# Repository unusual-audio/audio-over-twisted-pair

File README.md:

# Simple audio over twisted pair adapter

A basic adapter box that can route 4 differential audio signals on TRS connectors over twisted pair cable (ideally S/FTP).

## Bill of materials (per unit)

- 1× Main PCB ([gerber files](https://github.com/unusual-audio/audio-over-twisted-pair/releases/download/revision1/PCB.zip))
- 1× Front panel PCB ([gerber files](https://github.com/unusual-audio/audio-over-twisted-pair/releases/download/revision1/Front.Panel.zip))
- 1× Rear panel PCB ([gerber files](https://github.com/unusual-audio/audio-over-twisted-pair/releases/download/revision1/Back.Panel.zip))
- 1× [Adafruit 2230](https://www.mouser.de/ProductDetail/485-2230) enclosure
- 1× [Amphenol RJHSE-5380](https://www.mouser.de/ProductDetail/523-RJHSE-5380) RJ45 connector
- 4× [Neutrik NRJ6HF](https://www.mouser.de/ProductDetail/550-20311) TRS connector
- 4× [Neutrik NRJ-NUT-B](https://www.mouser.de/ProductDetail/550-1005) nut for TRS connector
- 8× M2.5x7 machine screw (Adafruit supplies counterunk screws, unsuitable for PCB panels)
- 4× Self-adhesive rubber feet (e.g. 3M Bumpons SJ 5076)

## Caveats

- This is a hobby project. Recreate at your own risk. (but if you do, send pictures to <unusualaudio@protonmail.com>)
- These are not necessarily compatible with similar commercial products as the wiring is not standardised.

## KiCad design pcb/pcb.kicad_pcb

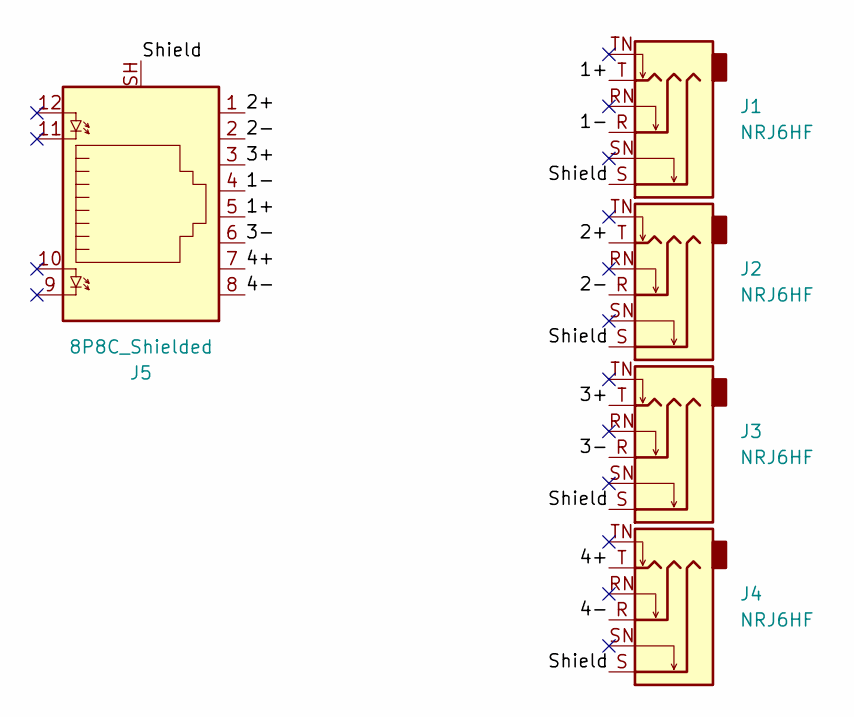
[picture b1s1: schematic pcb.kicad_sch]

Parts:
J1, J2, J3, J4: NRJ6HF; Jack_6.35mm_Neutrik_NRJ6HF_Horizontal_No_Outline
J5: 8P8C_Shielded; RJ45_Amphenol_RJHSE538X

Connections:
/1+: J1.T, J5.5
/1-: J1.R, J5.4
/2+: J2.T, J5.1
/2-: J2.R, J5.2
/3+: J3.T, J5.3
/3-: J3.R, J5.6
/4+: J4.T, J5.7
/4-: J4.R, J5.8
/Shield: J1.S, J2.S, J3.S, J4.S, J5.SH

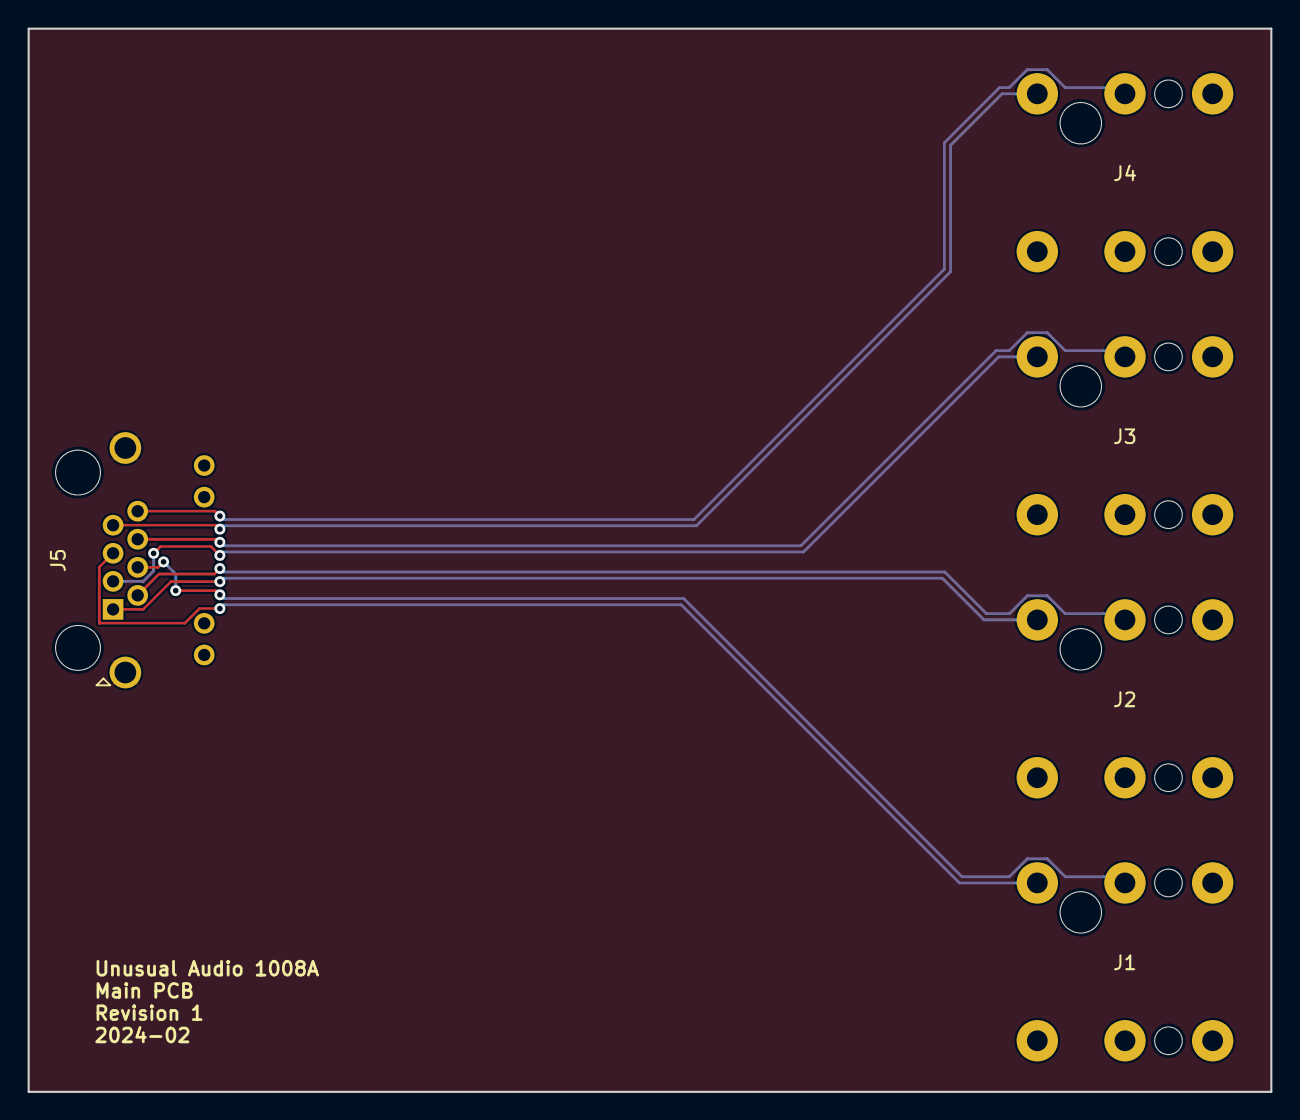
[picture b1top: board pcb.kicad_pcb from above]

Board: 2 copper layers, 90.0 x 77.0 mm, 5 parts (0 on the bottom side), 9 nets.

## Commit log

2024-06-03 Revision 1
